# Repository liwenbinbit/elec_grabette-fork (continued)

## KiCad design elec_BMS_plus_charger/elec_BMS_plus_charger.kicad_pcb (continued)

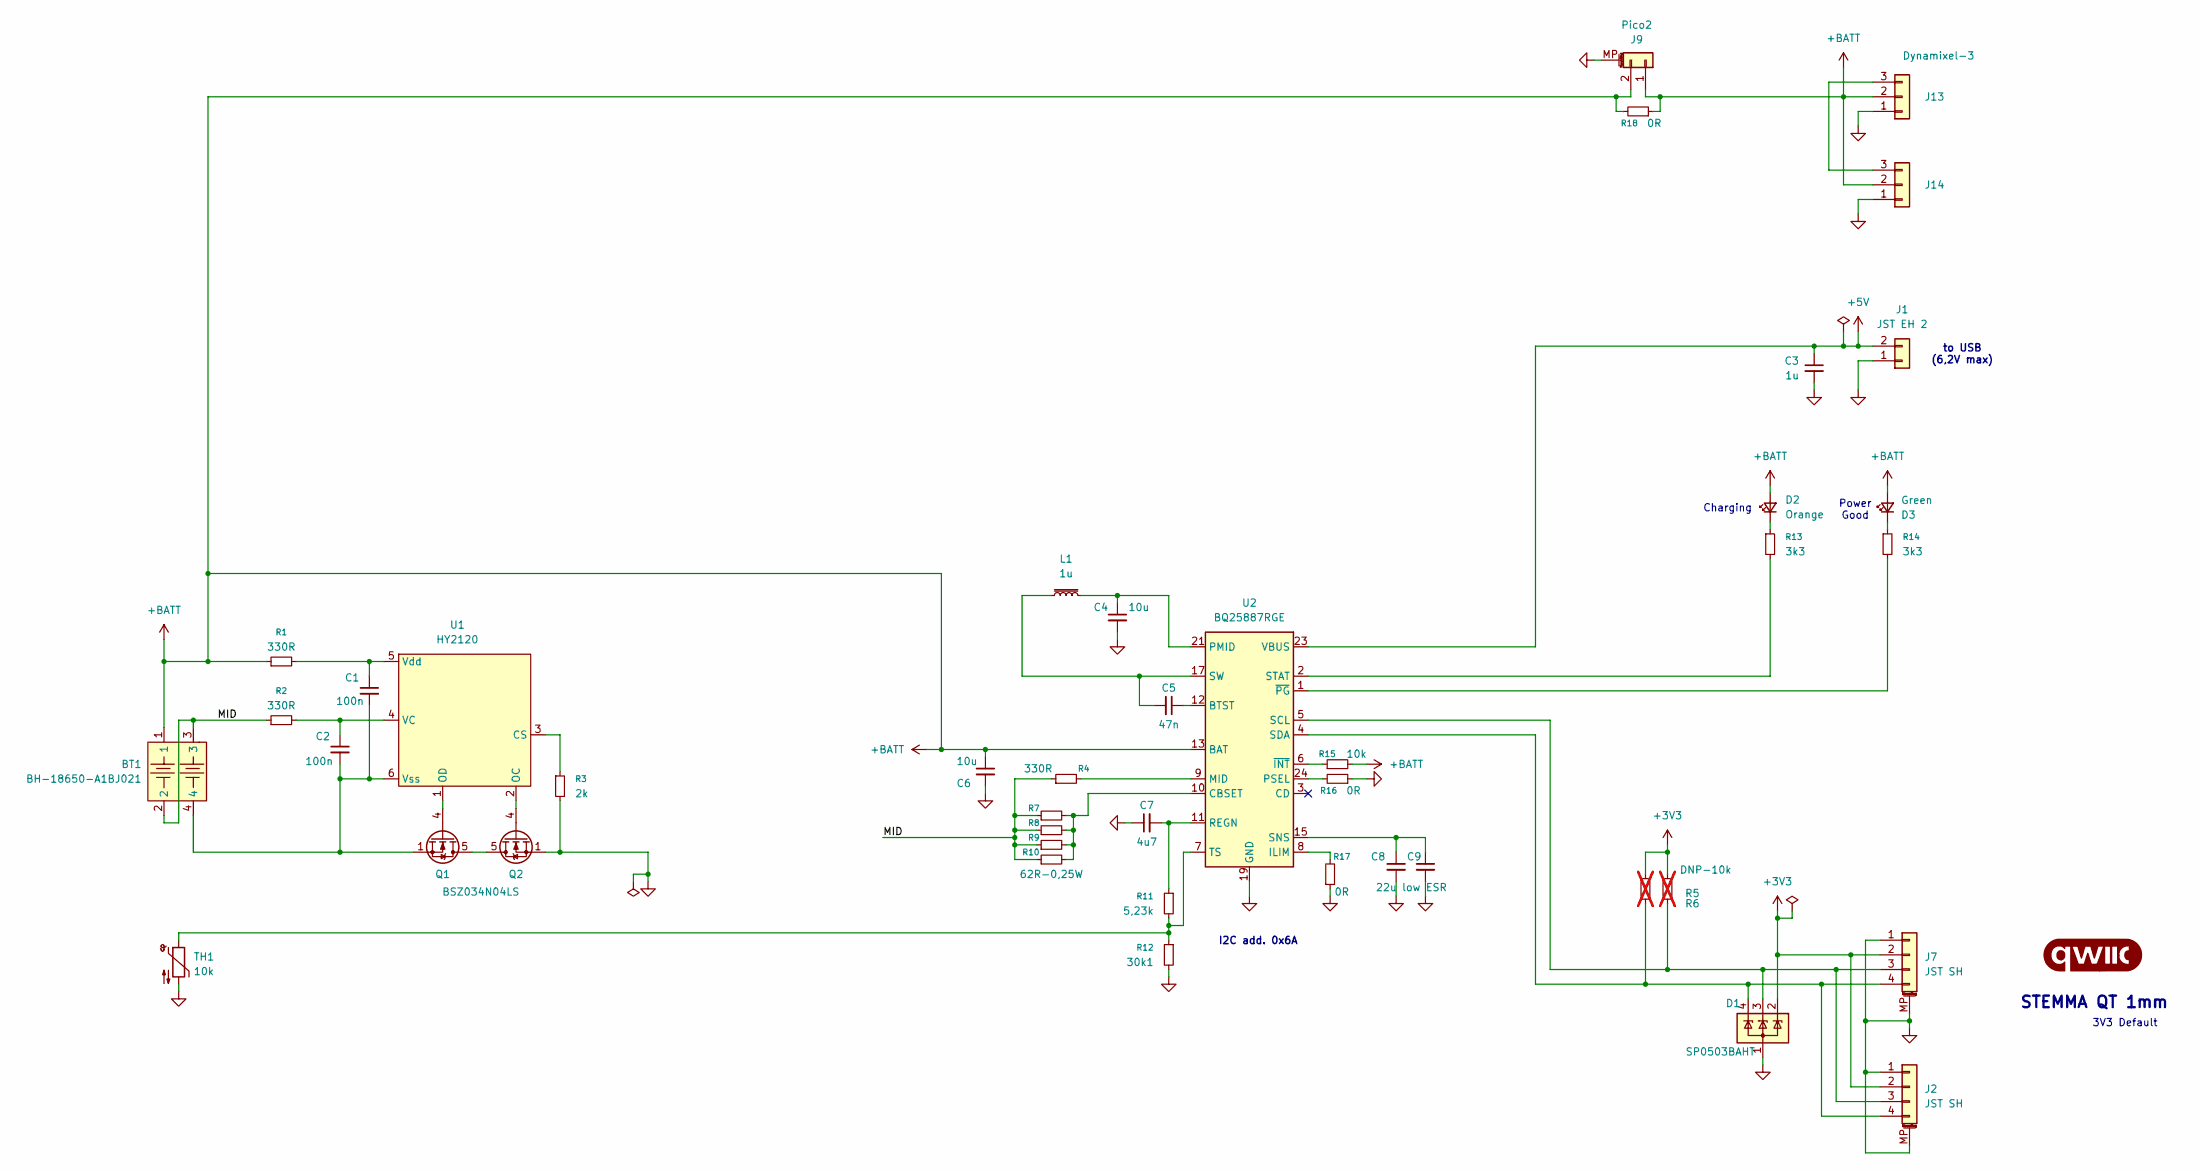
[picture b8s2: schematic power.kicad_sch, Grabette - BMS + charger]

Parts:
BT1: BH-18650-A1BJ021; BAT-TH_L77.0-W39.9_BH-18650-A1BJ021; LCSC Part C20606804
C1, C2: 100n; C_0402_1005Metric; LCSC Part C1525
C3: 1u; C_0402_1005Metric; LCSC Part C52923
C4, C6: 10u; C_0603_1608Metric; LCSC Part C19702
C5: 47n; C_0402_1005Metric; LCSC Part C272875
C7: 4u7; C_0603_1608Metric; LCSC Part C1705
C8, C9: 22u low ESR; C_0805_2012Metric; LCSC Part C5674
D1: SP0503BAHT; SOT-143; LCSC Part C41364459
D2: Orange; LED_0603_1608Metric; LCSC Part C84269
D3: Green; LED_0603_1608Metric; LCSC Part C19171301
G1: qwiic_Logo; Logo_qwiic_5mm
J1: JST EH 2; JST_EH_B2B-EH-A_1x02_P2.50mm_Vertical; LCSC Part C160262
J2, J7: JST SH; JST_SH_BM04B-SRSS-TB_1x04-1MP_P1.00mm_Vertical; LCSC Part C160390
J9: Pico2; Molex_PicoBlade_53047-0210_1x02_P1.25mm_Vertical
J13, J14: Dynamixel-3; JST_EH_B3B-EH-A_1x03_P2.50mm_Vertical; LCSC Part C160259
L1: 1u; C_0402_1005Metric; LCSC Part C52923
Q1, Q2: BSZ034N04LS; PQFN_3.3x3.3mm_-_PG-TDSON-8_FL; LCSC Part C534652
R1, R2, R4: 330R; R_0402_1005Metric; LCSC Part C25104
R3: 2k; R_0402_1005Metric; LCSC Part C2909344
R5, R6: DNP-10k; R_0402_1005Metric; not fitted
R7, R8, R9, R10: 62R-0,25W; R_1206_3216Metric; LCSC Part C3013271
R11: 5,23k; R_0402_1005Metric; LCSC Part C2933105
R12: 30k1; R_0402_1005Metric; LCSC Part C2998131
R13, R14: 3k3; R_0402_1005Metric; LCSC Part C25890
R15: 10k; R_0402_1005Metric; LCSC Part C2906861
R16, R17: 0R; R_0402_1005Metric; LCSC Part C17168
R18: 0R; R_0603_1608Metric; LCSC Part C21189
TH1: 10k; R_0402_1005Metric; LCSC Part C2906861
U1: HY2120; SOT-23-6; LCSC Part C168778
U2: BQ25887RGE; Texas_RGE0024H_VQFN-24-1EP_4x4mm_P0.5mm_EP2.7x2.7mm; LCSC Part C2761614

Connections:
+3V3: D1.2 (K), J2.2, J7.2, R5.1, R6.1
+5V: C3.1, J1.2, U2.23 (VBUS)
+BATT: BT1.1, C6.1, D2.2 (A), D3.2 (A), J9.1, J9.2, J13.2, J14.2, R1.1, R15.2, R18.1, R18.2, U2.13 (BAT), U2.14 (BAT)
/Power/MID: BT1.2, BT1.3, R2.1, R4.1, R7.1, R8.1, R9.1, R10.1
GND: C3.2, C4.2, C6.2, C7.1, C8.2, C9.2, D1.1 (A), J1.1, J2.1, J2.MP (MountPin), J7.1, J7.MP (MountPin), J9.MP (MountPin), J13.1, J14.1, Q2.1 (S), R3.2, R12.2, R16.1, R17.1, TH1.2, U2.19 (GND), U2.20 (GND), U2.25 (GND); also elsewhere on the board
unnamed: C4.1, L1.2, U2.21 (PMID), U2.22 (PMID)
unnamed: C5.2, L1.1, U2.17 (SW), U2.18 (SW)
unnamed: C8.1, C9.1, U2.15 (SNS), U2.16 (SNS)
unnamed: D2.1 (K), R13.1
unnamed: D3.1 (K), R14.1
unnamed: D1.3 (K), J2.3, J7.3, R5.2, U2.5 (SCL)
unnamed: D1.4 (K), J2.4, J7.4, R6.2, U2.4 (SDA)
unnamed: J13.3, J14.3
unnamed: Q1.5 (D), Q2.5 (D)
unnamed: Q1.4 (G), U1.1 (OD)
unnamed: BT1.4, C1.2, C2.2, Q1.1 (S), U1.6 (Vss)
unnamed: Q2.4 (G), U1.2 (OC)
unnamed: R3.1, U1.3 (CS)
unnamed: C2.1, R2.2, U1.4 (VC)
unnamed: C1.1, R1.2, U1.5 (Vdd)
unnamed: C5.1, U2.12 (BTST)
unnamed: R7.2, R8.2, R9.2, R10.2, U2.10 (CBSET)
unnamed: R17.2, U2.8 (ILIM)
unnamed: R4.2, U2.9 (MID)
unnamed: R16.2, U2.24 (PSEL)
unnamed: C7.2, R11.1, U2.11 (REGN)
unnamed: R13.2, U2.2 (STAT)
unnamed: R11.2, R12.1, TH1.1, U2.7 (TS)
unnamed: R15.1, U2.6 (~INT)
unnamed: R14.2, U2.1 (~PG)

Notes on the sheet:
Power Good
to USB (6,2V max)
STEMMA QT 1mm
I2C add. 0x6A
Charging
3V3 Default

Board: 2 copper layers, 52 parts (37 on the bottom side), 30 nets, no tracks yet.

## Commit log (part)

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2026-03-12 [init] Initial commit
2026-03-12 [added] elec_IMU
2026-03-17 [update] Full schematic + positionning
2026-03-17 [update] Angle+IMU are routed ERC OK
2026-03-17 [update] IMU + angle sensor RC1
2026-03-17 [added] Wiring Diagrams
2026-03-18 [added] Gripette-specific DCDC
2026-03-20 [added] BMS/Charger
2026-03-23 [update] BMS schematic DRC 0k.
2026-03-25 [update] Mechanical adaptations.
2026-03-25 [update] OK for JLC
2026-04-09 [added] Gripette USB hub + DCDC
2026-04-10 [update] sch reviewed by Claude
2026-04-15 [update] Gripette hub routed
2026-04-15 [added] XT60-USB-C Bulkhead for Gripette, JLC ready.
2026-04-16 [update] Gripette bulkhead ready for production.
2026-04-16 [uptate] Gripette hub ok for JLC
2026-04-17 [update] Release A1, small batch @JLC
2026-04-29 [update] BMS+charger DRC OK
2026-05-03 [update] move BMS+charger to a dedicated repo.
2026-05-26 [update] Added error to gripette, going to B1
2026-05-28 [update] SCH B1-RC1
2026-05-29 [update] SCH + PCB B1-RC1
2026-06-01 [update] Before review
2026-06-01 [update] review by Claude. Corrections, RC2
2026-06-02 [update] gripette + bulkhead -B1 in production @JLCPCB
2026-06-30 [fix] Ajusting cable length
